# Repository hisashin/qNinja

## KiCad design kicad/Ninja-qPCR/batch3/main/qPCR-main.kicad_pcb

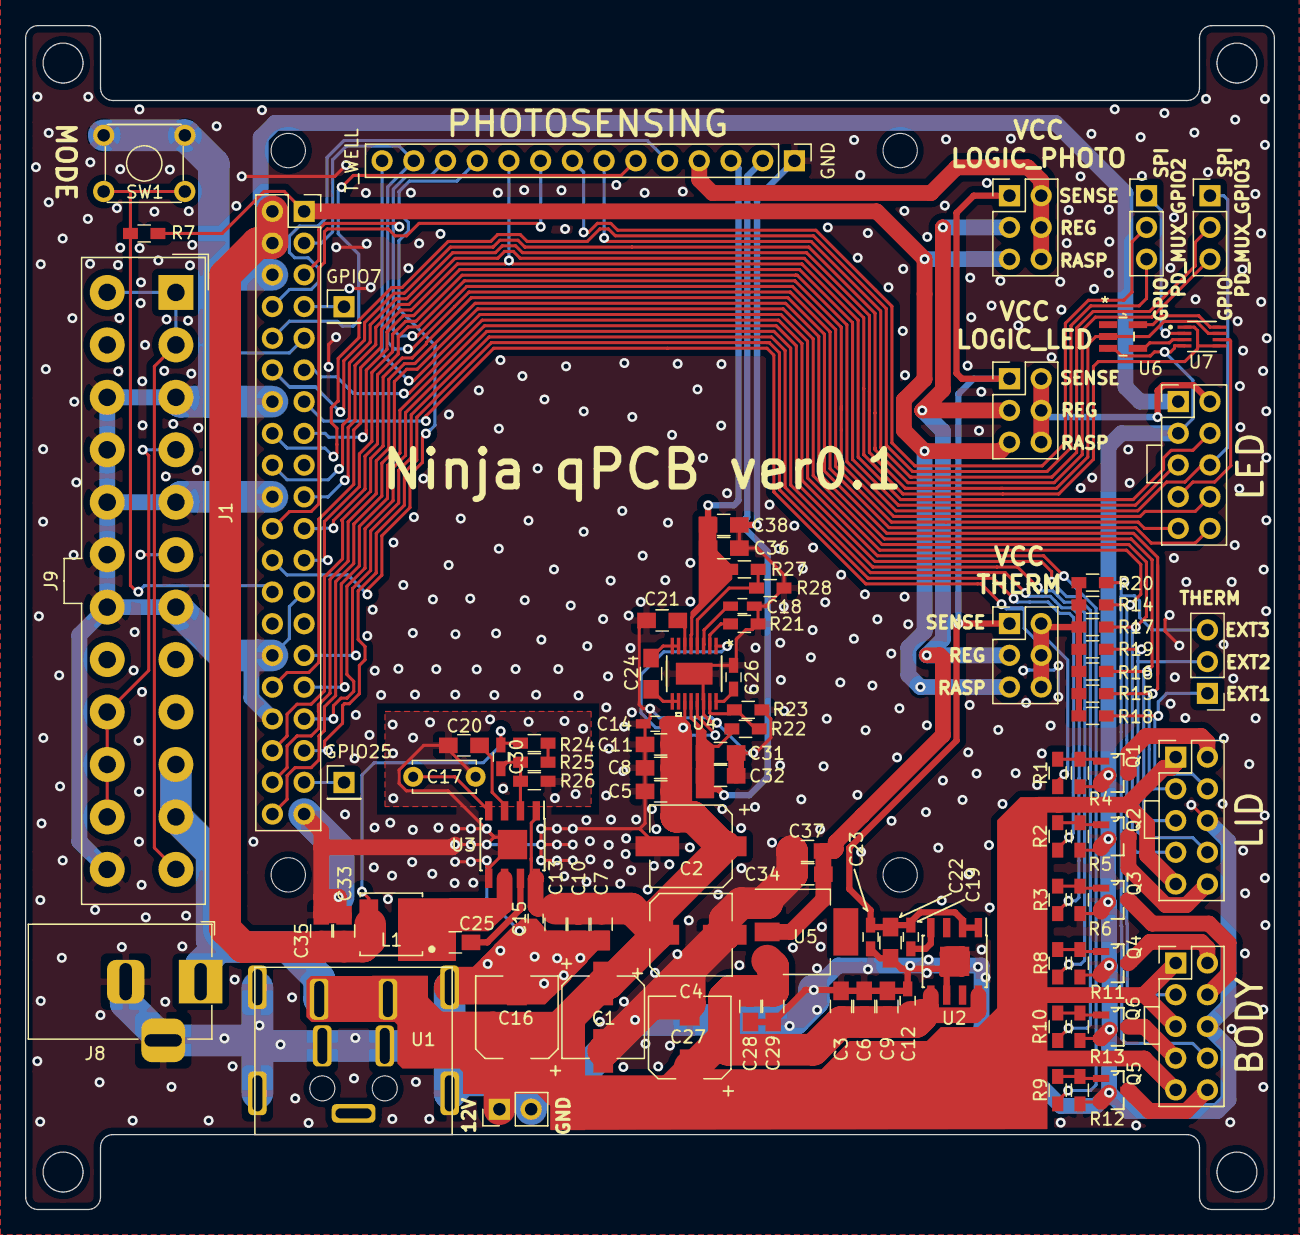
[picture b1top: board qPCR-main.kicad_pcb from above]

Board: 2 copper layers, 100.0 x 94.8 mm, 97 parts (0 on the bottom side), 76 nets.

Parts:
BODY: Conn_02x05; Con_2x05
C1, C2, C4, C16, C27: 100uF; CP_Elec_6.3x5.8
C3, C5, C6, C22, C28, C33, C34, C35: 22uF; C_0805_HandSoldering
C7, C8, C10, C21, C31, C36: 10uF; C_0805_HandSoldering
C9, C11, C13, C25, C29, C32, C37, C38: 0.1uF; C_0805_HandSoldering
C12, C14, C15, C18, C19, C26: 0.01uF; C_0603_HandSoldering
C17: 3300pF; C_Disc_D5.0mm_W2.5mm_P5.00mm
C20, C24: 1uF; C_0805_HandSoldering
C23: 820pF; C_0603_HandSoldering
C30: (5-100pF); C_0603_HandSoldering
GPIO7, GPIO25: Conn_01x01_Male; Pin_Header_Straight_1x01_Pitch2.54mm
J1: Raspberry_Pi_3A_Plus_wpi; Raspberry_Pi_3A+_Socketed_THT_FaceDown_MountingHoles_minimum
J2, J10, J11: Conn_01x03_Male; Pin_Header_Straight_1x03_Pitch2.54mm
J5, J6, J7: Conn_02x03_Odd_Even; Pin_Header_Straight_2x03_Pitch2.54mm
J8: Barrel_Jack_Switch; BarrelJack_Horizontal
J9: ATX-24; Molex_MiniFit-JR-5556-24A_2x12x4.20mm_Straight
J_12V1: Conn_01x02_Male; Pin_Header_Straight_1x02_Pitch2.54mm
L1: 3.3uH(ALPS GLMC / TDK SPM6530); IND_VLS5045EX-4R7M
LED: Conn_02x05; Con_2x05
LID: Conn_02x05; Con_2x05
PHOTOSENSING: Conn_01x14_Male; Pin_Header_Straight_1x14_Pitch2.54mm
Q1, Q2, Q3, Q4, Q5, Q6: Q_NMOS_GSD; SOT95P240X112-3N
R1, R2, R3, R8, R9, R10: 1k; R_0603_HandSoldering
R4, R5, R6, R7, R11, R12, R13: 10k; R_0603_HandSoldering
R14, R15, R16, R17, R18, R19, R20: R; R_0603_HandSoldering
R21: 100K; R_0603_HandSoldering
R22, R27: 22X; R_0603_HandSoldering
R23, R28: 3X; R_0603_HandSoldering
R24: 120k; R_0603_HandSoldering
R25: 1.8k/0; R_0603_HandSoldering
R26: 22k; R_0603_HandSoldering
SW1: TACTILE_4; SW_TH_Tactile_Omron_B3F-10xx
U1: DIN4_PWR; DN4_PWR
U2: IFX1763; SOIC-8-1EP_3.9x4.9mm_Pitch1.27mm
U3: BD9D320EFJ-E2; SOIC-8-1EP_3.9x4.9mm_Pitch1.27mm
U4: LTC3260EMSE-TRPBF
U5: CJT1117-3.3; SOT-223
U6: SN74LVC1G04DBVR
U7: SN74LVC2G66DCUR

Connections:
3V3_REG: C34.1, C37.1, J5.3, J6.3, J7.3, U5.2
3V3_SENSE: C19.1, C22.1, C23.1, J5.1, J6.1, J7.1, U2.1, U2.2
5V: C30.1, C33.1, C35.1, J1.2, J1.4, L1.2, LED.1, R24.1
12V: BODY.1, BODY.5, BODY.9, C1.1, C2.1, C3.1, C4.1, C5.1, C6.1, C7.1, C8.1, C9.1, C10.1, C11.1, C12.1, C13.1, C14.1, C15.1, C16.1, C27.1, C28.1, C29.1, J8.1, J9.10, J9.11, J_12V1.1, LID.1, LID.9, U1.1, U1.2, U2.5, U2.8, U3.1, U3.8, U4.1, U4.11, U4.13, U5.3
+10V: C31.1, C32.1, PHOTOSENSING.2, R22.1, U4.12
-10V: C36.1, C38.1, PHOTOSENSING.3, R27.1, U4.5
/3V3_RASP: J1.1, J5.5, J6.5, J7.5, R7.2
/FAN1: J1.29, R3.2
/FAN2: J1.31, R10.2
/LID_HEATER1: J1.13, R1.2
/LID_HEATER2: J1.35, R2.2
/SheetPower/ADJ+: R22.2, R23.1, U4.15
/SheetPower/ADJ-: R27.2, R28.1, U4.4
/SheetPower/BD_BOOT: C25.1, U3.7
/SheetPower/BD_FB: C30.2, R25.2, R26.1, U3.2
/SheetPower/BD_SW: C25.2, L1.1, U3.6
/SheetPower/C-: C24.2, U4.7, U4.8
/SheetSPI/SPI_SWITCH_INV: U6.4, U7.3
/VCC_LOGIC_LED: J6.2, J6.4, J6.6, LED.2
/VCC_LOGIC_PHOTO: J7.2, J7.4, J7.6, PHOTOSENSING.4
/VCC_THERM: J5.2, J5.4, J5.6, R14.2, R15.2, R16.2, R17.2, R18.2, R19.2, R20.2
/WELL_HEATER1: J1.33, R8.2
/WELL_HEATER2: J1.11, R9.2
ADC_DRDY: J1.24, PHOTOSENSING.11
BODY_HEATER1B: BODY.2, Q4.3
BODY_HEATER2B: BODY.10, Q5.3
FAN_BLACK_GND1: BODY.4, Q3.3
FAN_BLACK_GND2: BODY.7, Q6.3
GND: BODY.6, C1.2, C2.2, C3.2, C4.2, C5.2, C6.2, C7.2, C8.2, C9.2, C10.2, C11.2, C12.2, C13.2, C14.2, C15.2, C16.2, C17.2, C18.2, C20.2, C21.2, C22.2, C23.2, C26.2, C27.2, C28.2, C29.2, C31.2, C32.2, C33.2, C34.2, C35.2, C36.2, C37.2, C38.2, J1.6, J1.9, J1.14, J1.20, J1.25, J1.30, J1.34, J1.39, J8.2, J8.3, J9.3, J9.5, J9.7, J9.15, J9.16, J9.17, J9.18, J9.19, J9.24, J_12V1.2, LED.3, LID.6, PHOTOSENSING.1, Q1.2, Q2.2, Q3.2, Q4.2, Q5.2, Q6.2, R4.1, R5.1, R6.1, R11.1, R12.1, R13.1, R21.2, R23.2, R26.2, R28.2, SW1.3, SW1.4, U1.3, U1.4, U1.6, U1.7, U1.8, U1.9, U2.6, U2.9, U3.5, U3.9, U4.14, U4.EPAD, U5.1, U6.3, U7.4
GPIO7: GPIO7.1, J1.7
GPIO25: GPIO25.1, J1.37
I2C_SCL: J1.5, LED.9, PHOTOSENSING.12
I2C_SDA: J1.3, LED.10, PHOTOSENSING.13
LED_LAT: J1.15, LED.5
LED_SPI_MOSI: LED.7, U7.6
LID_HEATER1B: LID.2, Q1.3
LID_HEATER2B: LID.10, Q2.3
unnamed: C17.1, U3.4
unnamed: C18.1, U4.3
unnamed: C19.2, U2.4
unnamed: C20.1, U3.3
unnamed: C21.1, U4.6
unnamed: C24.1, U4.9, U4.10
unnamed: C26.1, U4.16
unnamed: J1.26, R7.1, SW1.1, SW1.2
unnamed: J9.1, J9.2, J9.12, J9.13
unnamed: J9.4, J9.6, J9.21, J9.22, J9.23
unnamed: Q1.1, R1.1, R4.2
unnamed: Q2.1, R2.1, R5.2
unnamed: Q3.1, R3.1, R6.2
unnamed: Q4.1, R8.1, R11.2
unnamed: Q5.1, R9.1, R12.2
unnamed: Q6.1, R10.1, R13.2
unnamed: R21.1, U4.2
unnamed: R24.2, R25.1
PD_MUX_GPIO1: J1.22, PHOTOSENSING.9
PD_MUX_GPIO2: J10.2, PHOTOSENSING.8
PD_MUX_GPIO2?: J1.16, J10.3
PD_MUX_GPIO3: J11.2, PHOTOSENSING.7
PD_MUX_GPIO3?: J1.12, J11.3
PD_MUX_GPIO4: J1.10, PHOTOSENSING.6
PD_MUX_GPIO5: J1.8, PHOTOSENSING.5
PD_MUX_SPI_MOSI: J10.1, U7.2
PD_REF_PWM: J1.32, LED.4, PHOTOSENSING.10
SPI_MISO: J1.21, LED.8
SPI_MOSI: J1.19, U7.1, U7.5
SPI_SCLK: J1.23, J11.1, LED.6
SPI_SWITCH: J1.18, U6.2, U7.7
THERM_AIR: J1.36, LID.3, R15.1
THERM_EXT1: J2.1, LID.4, R18.1
THERM_EXT2: J2.2, LID.8, R19.1
THERM_EXT3: BODY.8, J2.3, R20.1
THERM_LID1: J1.38, LID.5, R16.1
THERM_LID2: J1.40, LID.7, R17.1
THERM_WELL: BODY.3, PHOTOSENSING.14, R14.1
VCC_LOGIC: U6.5, U7.8

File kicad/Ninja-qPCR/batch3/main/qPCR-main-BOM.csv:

"Id";"Designator";"Package";"Quantity";"Designation";"Supplier and ref";
1;"J1";"Raspberry_Pi_3A+_Socketed_THT_FaceDown_MountingHoles_minimum";1;"Raspberry_Pi_3A_Plus_wpi";;;
2;"R16,R14,R15,R17,R18,R19,R20";"R_0603_HandSoldering";7;"R";;;
3;"BODY1,LED,LID";"Con_2x05";3;"Conn_02x05";;;
4;"C1,C2,C4,C16,C27";"CP_Elec_6.3x5.8";5;"100uF";;;
5;"C3,C5,C6,C22,C28,C33,C34,C35";"C_0805_HandSoldering";8;"22uF";;;
6;"C7,C8,C10,C21,C31,C36";"C_0805_HandSoldering";6;"10uF";;;
7;"C9,C11,C13,C25,C29,C32,C37,C38";"C_0805_HandSoldering";8;"0.1uF";;;
8;"C12,C14,C15,C18,C19,C26";"C_0603_HandSoldering";6;"0.01uF";;;
9;"C17";"C_Disc_D5.0mm_W2.5mm_P5.00mm";1;"3300pF";;;
10;"C20,C24";"C_0805_HandSoldering";2;"1uF";;;
11;"C23";"C_0603_HandSoldering";1;"820pF";;;
12;"C30";"C_0603_HandSoldering";1;"(5-100pF)";;;
13;"J2,J10,J11";"Pin_Header_Straight_1x03_Pitch2.54mm";3;"Conn_01x03_Male";;;
14;"GPIO7,GPIO25";"Pin_Header_Straight_1x01_Pitch2.54mm";2;"Conn_01x01_Male";;;
15;"J5,J6,J7";"Pin_Header_Straight_2x03_Pitch2.54mm";3;"Conn_02x03_Odd_Even";;;
16;"J8";"BarrelJack_Horizontal";1;"Barrel_Jack_Switch";;;
17;"J9";"Molex_MiniFit-JR-5556-24A_2x12x4.20mm_Straight";1;"ATX-24";;;
18;"J_12V1";"Pin_Header_Straight_1x02_Pitch2.54mm";1;"Conn_01x02_Male";;;
19;"L1";"IND_VLS5045EX-4R7M";1;"3.3uH(ALPS GLMC / TDK SPM6530)";;;
20;"PHOTOSENSING";"Pin_Header_Straight_1x14_Pitch2.54mm";1;"Conn_01x14_Male";;;
21;"Q1,Q2,Q3,Q4,Q5,Q6";"SOT95P240X112-3N";6;"Q_NMOS_GSD";;;
22;"R1,R2,R3,R8,R9,R10";"R_0603_HandSoldering";6;"1k";;;
23;"R4,R5,R6,R7,R11,R12,R13";"R_0603_HandSoldering";7;"10k";;;
24;"R22,R27";"R_0603_HandSoldering";2;"22X";;;
25;"R23,R28";"R_0603_HandSoldering";2;"3X";;;
26;"R24";"R_0603_HandSoldering";1;"120k";;;
27;"R25";"R_0603_HandSoldering";1;"1.8k/0";;;
28;"R26";"R_0603_HandSoldering";1;"22k";;;
29;"U1";"DN4_PWR";1;"DIN4_PWR";;;
30;"U2";"SOIC-8-1EP_3.9x4.9mm_Pitch1.27mm";1;"IFX1763";;;
31;"U3";"SOIC-8-1EP_3.9x4.9mm_Pitch1.27mm";1;"BD9D320EFJ-E2";;;
32;"U4";"LTC3260EMSE-TRPBF";1;"LTC3260EMSE-TRPBF";;;
33;"U5";"SOT-223";1;"CJT1117-3.3";;;
34;"U6";"SN74LVC1G04DBVR";1;"SN74LVC1G04DBVR";;;
35;"U7";"SN74LVC2G66DCUR";1;"SN74LVC2G66DCUR";;;
36;"R21";"R_0603_HandSoldering";1;"100K";;;
37;"SW1";"SW_TH_Tactile_Omron_B3F-10xx";1;"TACTILE_4";;;

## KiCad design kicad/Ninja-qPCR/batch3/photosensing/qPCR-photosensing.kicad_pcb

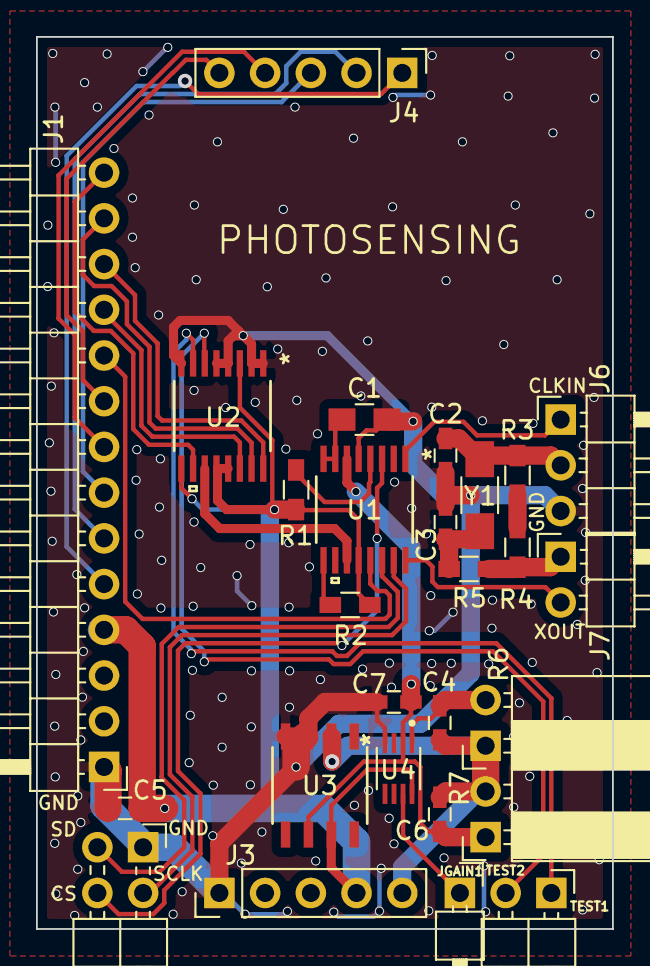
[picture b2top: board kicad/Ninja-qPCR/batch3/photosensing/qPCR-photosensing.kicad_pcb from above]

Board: 2 copper layers, 32.0 x 49.6 mm, 27 parts (0 on the bottom side), 31 nets.

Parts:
C1: 1uF; C_0805_HandSoldering
C2, C3: 10pF; C_0603_HandSoldering
C4, C6: 22pF; C_0603_HandSoldering
C5, C7: 0.1uF; C_0603_HandSoldering
J1: Conn_01x14_Male; Pin_Header_Angled_1x14_Pitch2.54mm
J3, J4: Conn_01x05_Male; Pin_Header_Straight_1x05_Pitch2.54mm
J6: Conn_01x03_Male; Pin_Header_Angled_1x03_Pitch2.54mm
J7: Conn_01x02_Male; Pin_Header_Angled_1x02_Pitch2.54mm
JGAIN1: Conn_01x01_Male; Pin_Header_Angled_1x01_Pitch2.54mm
JSPI1: Conn_01x04_Male; Pin_Header_Angled_2x02_Pitch2.54mm
JTHERM1: Conn_01x02_Male; Pin_Header_Angled_1x02_Pitch2.54mm
R1, R2: 10K; R_0603_HandSoldering
R3, R4: 10M; R_0603_HandSoldering
R5: 560k; R_0603_HandSoldering
R6, R7: R; Socket_Strip_Angled_1x02_Pitch2.54mm
U1: ADA2200ARUZ
U2: ADS1219IPWR
U3: LT1006S8-TRPBF
U4: SN74LVC2G66DCUR
Y1: 32.768kHz; C_1206_HandSoldering

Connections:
/AMP_GAIN_SW: JGAIN1.1, U4.7
/AMP_OUT: C6.1, C7.2, R7.1, U1.6, U3.6, U4.2
/CLKIN: J6.1, U1.1
/PHOTO_OUT: U1.11, U2.11
/XOUT: J7.2, U1.16
ADC_DRDY: J1.11, U2.14
DEMOD_SPI_CS: JSPI1.4, U1.3
DEMOD_SPI_SCLK: JSPI1.2, U1.15
DEMOD_SPI_SDIO: JSPI1.3, U1.14
GND: C1.2, C2.2, C3.2, C5.2, C7.1, J1.1, J3.1, J6.3, JSPI1.1, U1.5, U2.1, U2.2, U2.4, U2.5, U2.8, U3.3, U3.4, U4.4
I2C_SCL: J1.12, U2.16
I2C_SDA: J1.13, U2.15
unnamed: C1.1, U1.7, U1.8
unnamed: C2.1, J6.2, R3.2, Y1.1
unnamed: C3.1, R5.2, Y1.2
unnamed: C4.1, R6.2, U4.1
unnamed: J7.1, R4.1, R5.1
unnamed: R1.1, U1.4
unnamed: R2.1, U1.9
unnamed: R3.1, R4.2
PD_MUX_GPIO1: J1.9, J4.5
PD_MUX_GPIO2: J1.8, J4.4
PD_MUX_GPIO3: J1.7, J4.3
PD_MUX_GPIO4: J1.6, J4.2
PD_MUX_GPIO5: J1.5, J4.1
PD_MUX_OUT: C4.2, C6.2, J3.5, R6.1, R7.2, U3.2
PD_REF_PWM: J1.10, U1.13
THERM_TEST1: JTHERM1.1, U2.7
THERM_TEST2: JTHERM1.2, U2.6
THERM_WELL: J1.14, U2.10
VCC_LOGIC: C5.1, J1.4, J3.4, R1.2, R2.2, U1.12, U2.3, U2.9, U2.12, U2.13, U3.7, U4.8

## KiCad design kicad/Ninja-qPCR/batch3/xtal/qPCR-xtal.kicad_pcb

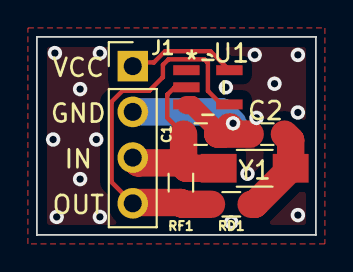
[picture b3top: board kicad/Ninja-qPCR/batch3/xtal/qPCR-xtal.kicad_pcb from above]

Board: 2 copper layers, 15.5 x 11.0 mm, 7 parts (0 on the bottom side), 5 nets.

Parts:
C1, C2: C; C_0603_HandSoldering
J1: Conn_01x04_Male; Pin_Header_Straight_1x04_Pitch2.54mm
RD1: ?; R_0603_HandSoldering
RF1: ?; R_0603_HandSoldering
U1: SN74LVC1G04DBVR
Y1: 32.768kHz?; C_1206_HandSoldering

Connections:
GND: C1.2, C2.2, J1.2, U1.3
IN: C1.1, J1.3, RF1.2, U1.2, Y1.1
unnamed: C2.1, RD1.2, Y1.2
OUT: J1.4, RD1.1, RF1.1, U1.4
VCC: J1.1, U1.5

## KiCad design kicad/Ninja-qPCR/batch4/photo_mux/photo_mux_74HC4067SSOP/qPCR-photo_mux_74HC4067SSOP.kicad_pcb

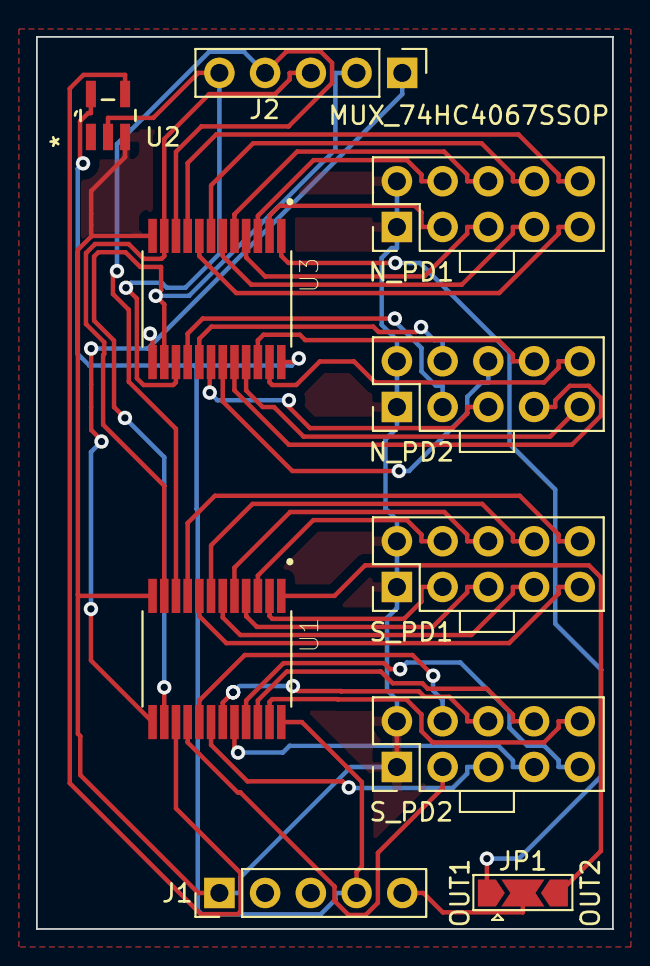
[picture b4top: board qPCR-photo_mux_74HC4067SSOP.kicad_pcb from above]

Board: 2 copper layers, 32.0 x 49.6 mm, 10 parts (0 on the bottom side), 43 nets.

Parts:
J1, J2: Conn_01x05_Male; Pin_Header_Straight_1x05_Pitch2.54mm
JP1: Jumper_3_Open; SolderJumper-3_P2.0mm_Open_TrianglePad1.0x1.5mm
N_PD1, N_PD2: Conn_02x05; Con_2x05
S_PD1, S_PD2: Conn_02x05; Con_2x05
U1, U3: CD74HC4067M96; SOP65P780X200-24N
U2: SN74LVC1G04DBVR

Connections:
/MUX_SELECT_INV: U1.15, U2.4
/PD_MUX_OUT1: JP1.1, U3.1
/PD_MUX_OUT2: JP1.3, U1.1
ADDRESSA0: J2.4, U1.10, U3.10
ADDRESSA1: J2.3, U1.11, U3.11
ADDRESSA2: J2.2, U1.14, U3.14
ADDRESSA3: J2.1, U1.13, U3.13
GND: J1.1, N_PD1.1, N_PD1.2, N_PD2.1, N_PD2.2, S_PD1.1, S_PD1.2, S_PD2.1, S_PD2.2, U1.12, U2.3, U3.12
MUX_SELECT: J2.5, U2.2, U3.15
N_PD1_OUT1: N_PD1.10, U3.9
N_PD1_OUT2: N_PD1.9, U3.8
N_PD1_OUT3: N_PD1.8, U3.7
N_PD1_OUT4: N_PD1.7, U3.6
N_PD1_OUT5: N_PD1.6, U3.5
N_PD1_OUT6: N_PD1.5, U3.4
N_PD1_OUT7: N_PD1.4, U3.3
N_PD1_OUT8: N_PD1.3, U3.2
N_PD1_OUT9: N_PD2.10, U3.23
N_PD1_OUT10: N_PD2.8, U3.22
N_PD1_OUT11: N_PD2.9, U3.21
N_PD1_OUT12: N_PD2.7, U3.20
N_PD1_OUT13: N_PD2.6, U3.19
N_PD1_OUT14: N_PD2.5, U3.18
N_PD1_OUT15: N_PD2.4, U3.17
N_PD1_OUT16: N_PD2.3, U3.16
PD_MUX_OUT: J1.5, JP1.2
S_PD1_OUT1: S_PD1.10, U1.9
S_PD1_OUT2: S_PD1.9, U1.8
S_PD1_OUT3: S_PD1.8, U1.7
S_PD1_OUT4: S_PD1.7, U1.6
S_PD1_OUT5: S_PD1.6, U1.5
S_PD1_OUT6: S_PD1.5, U1.4
S_PD1_OUT7: S_PD1.4, U1.3
S_PD1_OUT8: S_PD1.3, U1.2
S_PD1_OUT9: S_PD2.10, U1.23
S_PD1_OUT10: S_PD2.8, U1.22
S_PD1_OUT11: S_PD2.9, U1.21
S_PD1_OUT12: S_PD2.7, U1.20
S_PD1_OUT13: S_PD2.6, U1.19
S_PD1_OUT14: S_PD2.5, U1.18
S_PD1_OUT15: S_PD2.4, U1.17
S_PD1_OUT16: S_PD2.3, U1.16
VCC_LOGIC: J1.4, U1.24, U2.5, U3.24

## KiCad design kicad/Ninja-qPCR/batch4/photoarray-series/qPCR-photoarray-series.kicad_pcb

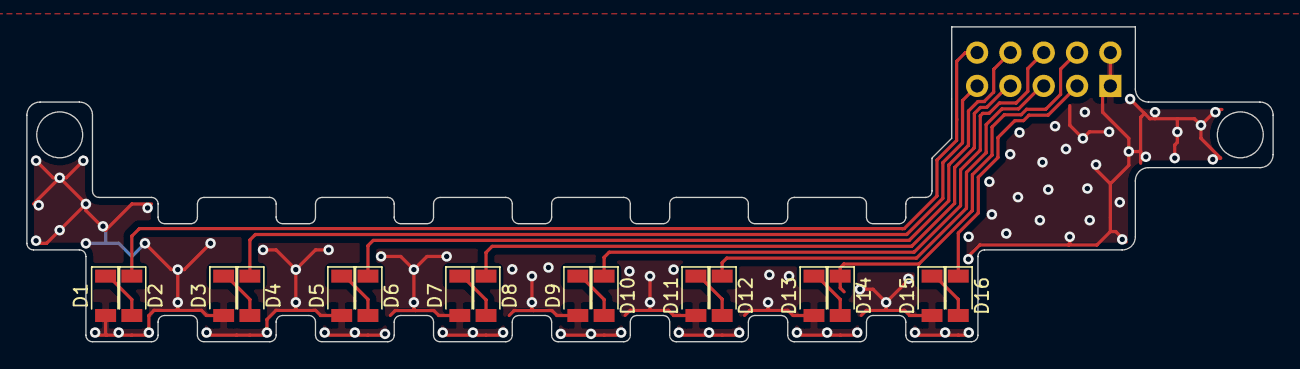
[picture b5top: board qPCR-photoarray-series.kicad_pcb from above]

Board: 2 copper layers, 95.0 x 24.0 mm, 17 parts (1 on the bottom side), 17 nets.

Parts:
D1, D2, D3, D4, D5, D6, D7, D8, D9, D10, D11, D12, D13, D14, D15, D16: D_Photo; D_1206
U1: Conn_02x05; Pin_Header_Straight_2x05_Pitch2.54mm

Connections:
GND: D1.2, D3.2, D5.2, D7.2, D9.2, D11.2, D13.2, D15.2, U1.1, U1.2
unnamed: D1.1, D2.2
unnamed: D3.1, D4.2
unnamed: D5.1, D6.2
unnamed: D7.1, D8.2
unnamed: D9.1, D10.2
unnamed: D11.1, D12.2
unnamed: D13.1, D14.2
unnamed: D15.1, D16.2
OUT1: D2.1, U1.10
OUT2: D4.1, U1.9
OUT3: D6.1, U1.8
OUT4: D8.1, U1.7
OUT5: D10.1, U1.6
OUT6: D12.1, U1.5
OUT7: D14.1, U1.4
OUT8: D16.1, U1.3

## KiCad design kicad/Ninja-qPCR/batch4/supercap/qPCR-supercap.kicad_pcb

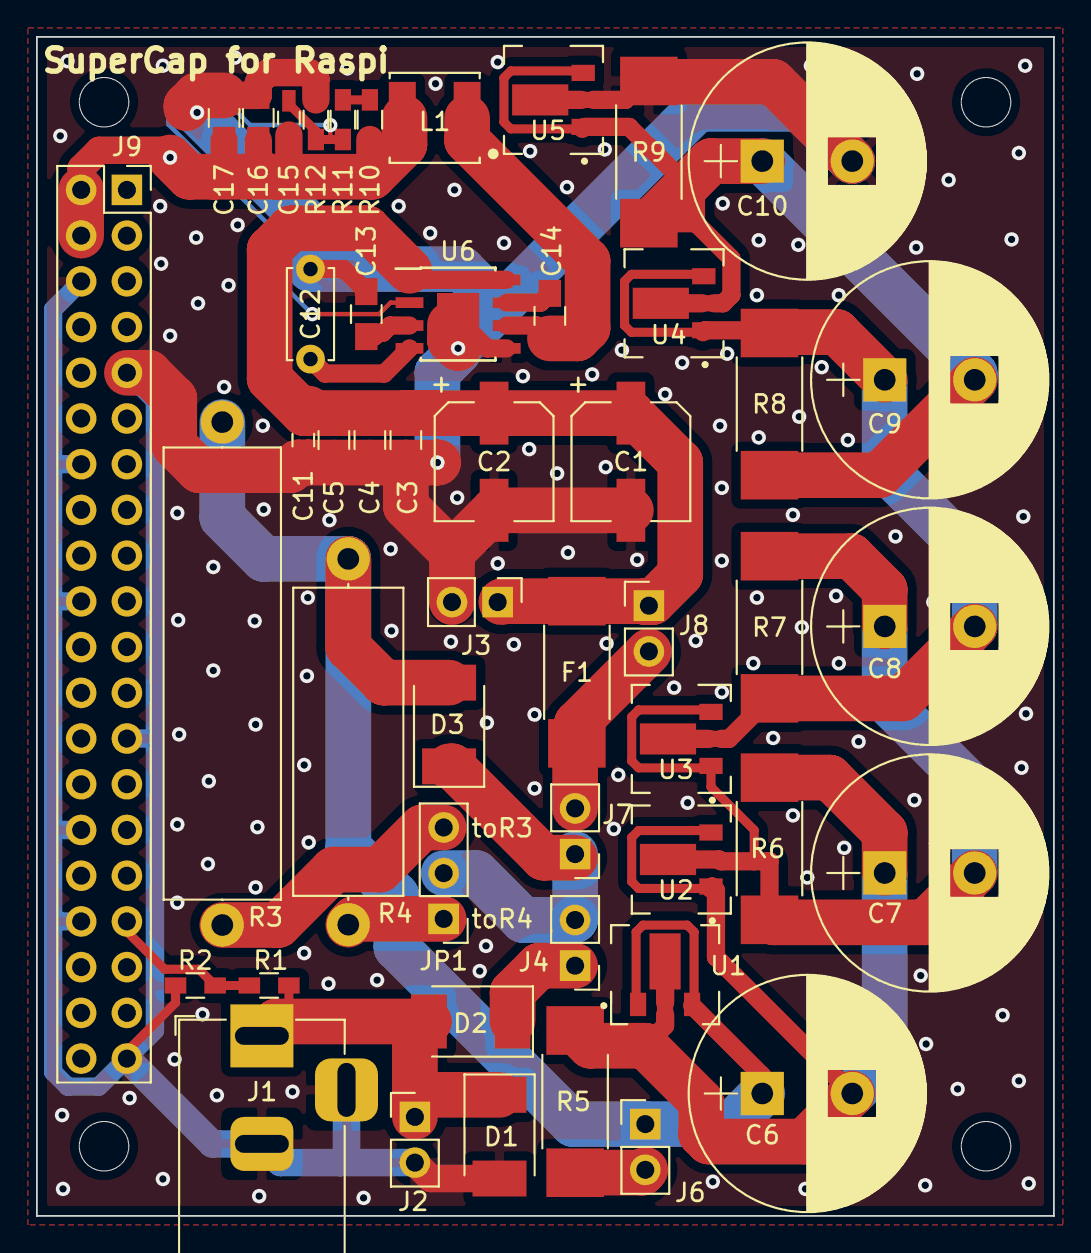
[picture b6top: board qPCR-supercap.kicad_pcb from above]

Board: 2 copper layers, 56.5 x 65.5 mm, 49 parts (0 on the bottom side), 22 nets.

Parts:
C1, C2: 100uF; CP_Elec_6.3x5.8
C3, C4: 10uF; C_0805_HandSoldering
C5, C14: 0.1uF; C_0805_HandSoldering
C6, C7, C8, C9, C10: 10F2.7V; CP_Radial_D13.0mm_P5.00mm
C11: 0.01uF; C_0603_HandSoldering
C12: 3300pF; C_Disc_D5.0mm_W2.5mm_P5.00mm
C13: 1uF; C_0805_HandSoldering
C15: (5-100pF); C_0603_HandSoldering
C16, C17: 22uF; C_0805_HandSoldering
D1: D_Schottky; D_2114
D2, D3: D; D_2114
F1: Fuse; R_2512_HandSoldering
J1: Barrel_Jack_Switch; BarrelJack_Horizontal
J2, J3, J4, J6, J7, J8: Conn_01x02_Male; Pin_Header_Straight_1x02_Pitch2.54mm
J9: Raspberry_Pi_3A_Plus_wpi; Raspberry_Pi_3A+_Socketed_THT_FaceDown_MountingHoles_minimum
JP1: Jumper_3_Open; Pin_Header_Straight_1x03_Pitch2.54mm
L1: 3.3uH(ALPS GLMC / TDK SPM6530); IND_VLS5045EX-4R7M
R1: 10k; R_0603_HandSoldering
R2: 2.2k; R_0603_HandSoldering
R3: 8.2Ω 3W; R_Axial_Power_L25.0mm_W6.4mm_P27.94mm
R4: 8.2Ω 3W; R_Axial_DIN0617_L17.0mm_D6.0mm_P20.32mm_Horizontal
R5, R6, R7, R8, R9: 1k?W; R_2512_HandSoldering
R10: 220k; R_0603_HandSoldering
R11: 0; R_0603_HandSoldering
R12: 39k; R_0603_HandSoldering
U1, U2, U3, U4, U5: TL431PK; NJM431U-ND
U6: BD9D320EFJ-E2; SOIC-8-1EP_3.9x4.9mm_Pitch1.27mm

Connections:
5V: C15.1, C16.1, C17.1, J9.2, J9.4, L1.2, R10.1
12V_BD_VIN: C1.1, C2.1, C3.1, C4.1, C5.1, C11.1, F1.1, J3.1, J8.1, U6.1, U6.8
/BD_BOOT: C14.1, U6.7
/BD_FB: C15.2, R11.2, R12.1, U6.2
/BD_SW: C14.2, L1.1, U6.6
GND: C1.2, C2.2, C3.2, C4.2, C5.2, C10.2, C11.2, C12.2, C13.2, C16.2, C17.2, D1.2, J1.2, J1.3, J2.2, J3.2, J9.6, J9.9, J9.14, J9.20, J9.25, J9.30, J9.34, J9.39, R2.2, R9.1, R12.2, U5.2, U5.2.1, U6.5, U6.9
unnamed: C6.1, D3.2, J6.1, R3.1, R4.1, U1.1, U1.3
unnamed: C6.2, C7.1, R5.2, R6.2, U1.2, U1.2.1, U2.1, U2.3
unnamed: C7.2, C8.1, R6.1, R7.2, U2.2, U2.2.1, U3.1, U3.3
unnamed: C8.2, C9.1, R7.1, R8.2, U3.2, U3.2.1, U4.1, U4.3
unnamed: C9.2, C10.1, R8.1, R9.2, U4.2, U4.2.1, U5.1, U5.3
unnamed: C12.1, U6.4
unnamed: C13.1, U6.3
unnamed: D2.1, J4.1
unnamed: D3.1, J4.2, J7.1, JP1.2
unnamed: F1.2, J7.2, J8.2
unnamed: J6.2, R5.1
unnamed: JP1.1, R4.2
unnamed: JP1.3, R3.2
unnamed: R10.2, R11.1
VIN: D1.1, D2.2, J1.1, J2.1, R1.1
VIN_SENSE: J9.33, R1.2, R2.1

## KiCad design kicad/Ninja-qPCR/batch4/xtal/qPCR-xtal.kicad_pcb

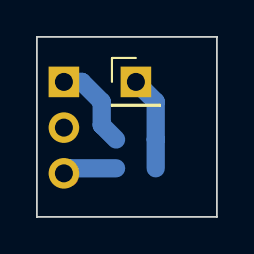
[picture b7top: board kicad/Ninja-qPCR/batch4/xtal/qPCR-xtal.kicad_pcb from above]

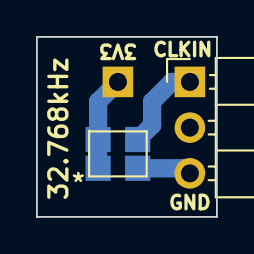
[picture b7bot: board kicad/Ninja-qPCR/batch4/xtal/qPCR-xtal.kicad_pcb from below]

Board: 2 copper layers, 10.0 x 10.0 mm, 3 parts (2 on the bottom side), 3 nets.

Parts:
J2: Conn_01x01_Male; Pin_Header_Straight_1x01_Pitch2.54mm
Jee: Conn_01x03_Male; Pin_Header_Angled_1x03_Pitch2.54mm
U1: COM1305-0.032768-EXT-T-TR

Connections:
3V3: J2.1, U1.1, U1.4
CLKIN: Jee.1, U1.3
GND: Jee.3, U1.2

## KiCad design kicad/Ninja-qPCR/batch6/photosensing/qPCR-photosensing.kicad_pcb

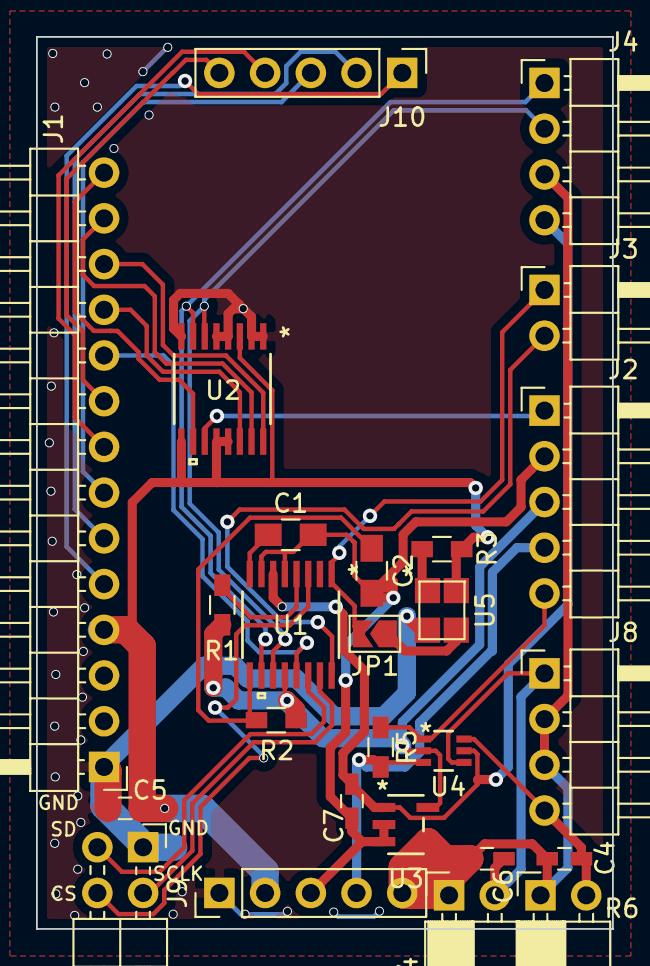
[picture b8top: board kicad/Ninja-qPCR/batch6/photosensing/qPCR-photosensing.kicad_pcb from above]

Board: 2 copper layers, 32.0 x 49.6 mm, 26 parts (0 on the bottom side), 33 nets.

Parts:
C1: 1uF; C_0805_HandSoldering
C2: 10uF; C_0805_HandSoldering
C4, C6: 22pF; C_0603_HandSoldering
C5, C7: 0.1uF; C_0603_HandSoldering
J1: Conn_01x14_Male; Pin_Header_Angled_1x14_Pitch2.54mm
J2: Conn_01x05_Male; Pin_Header_Angled_1x05_Pitch2.54mm
J3: Conn_01x02_Male; Pin_Header_Angled_1x02_Pitch2.54mm
J4, J8: Conn_01x04_Male; Pin_Header_Angled_1x04_Pitch2.54mm
J9, J10: Conn_01x05_Female; Pin_Header_Straight_1x05_Pitch2.54mm
JP1: Jumper; SolderJumper-2_P1.3mm_Open_TrianglePad1.0x1.5mm
JSPI1: Conn_01x04_Male; Pin_Header_Angled_2x02_Pitch2.54mm
R1, R2, R3: 10K; R_0603_HandSoldering
R4, R6: R; Socket_Strip_Angled_1x02_Pitch2.54mm
R5: R; R_0603_HandSoldering
U1: ADA2200ARUZ
U2: ADS1219IPWR
U3: AD8605ARTZ-R2
U4: TS5A9411DCKR
U5: COM1305-0.032768-EXT-T-TR

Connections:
-1V: J2.4, J9.4, R5.2, U4.3
/AMP_GAIN_SW: J2.5, R5.1, U4.1
/AMP_OUT: C7.2, J4.4, U1.6, U3.1, U4.5
/GAIN_LARGE: C6.1, J8.1, R4.2, U4.4
/GAIN_SMALL: C4.1, J8.4, R6.2, U4.6
/PHOTO_OUT_N: J4.1, U1.10, U2.7
/PHOTO_OUT_P: J4.2, U1.11, U2.6
ADC_DRDY: J1.11, U2.14
CLKIN: J3.1, JP1.2, U1.1
DEMOD_SPI_CS: JSPI1.4, U1.3
DEMOD_SPI_SCLK: JSPI1.2, U1.15
DEMOD_SPI_SDIO: JSPI1.3, U1.14
GND: C5.2, J1.1, J9.1, JSPI1.1, U2.1, U2.2, U2.4, U2.5, U2.8, U5.2
I2C_SCL: J1.12, U2.16
I2C_SDA: J1.13, U2.15
unnamed: C1.1, U1.8
unnamed: C2.1, R2.1, U1.9
unnamed: JP1.1, U5.3
unnamed: R1.1, U1.4
unnamed: R3.1, U5.1
PD_MUX_GPIO1: J1.9, J10.5
PD_MUX_GPIO2: J1.8, J10.4
PD_MUX_GPIO3: J1.7, J10.3
PD_MUX_GPIO4: J1.6, J10.2
PD_MUX_GPIO5: J1.5, J10.1
PD_MUX_OUT: C4.2, C6.2, J4.3, J8.2, J8.3, J9.5, R4.1, R6.1, U3.4
PD_REF_PWM: J1.10, U1.13
PHOTO_3V3: J2.3, R1.2, R2.2, U1.12, U3.5, U4.2
PHOTO_GND: C1.2, C2.2, C7.1, J2.2, J9.3, U1.5, U1.7, U3.2, U3.3
THERM_TEST1: J2.1, U2.11
THERM_WELL: J1.14, U2.10
VCC_LOGIC: C5.1, J1.4, J9.2, R3.2, U2.3, U2.9, U2.12, U2.13, U5.4
XOUT: J3.2, U1.16

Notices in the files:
parts and their libraries:
Copyright 2016 Accelerated Designs. All rights reserved.
